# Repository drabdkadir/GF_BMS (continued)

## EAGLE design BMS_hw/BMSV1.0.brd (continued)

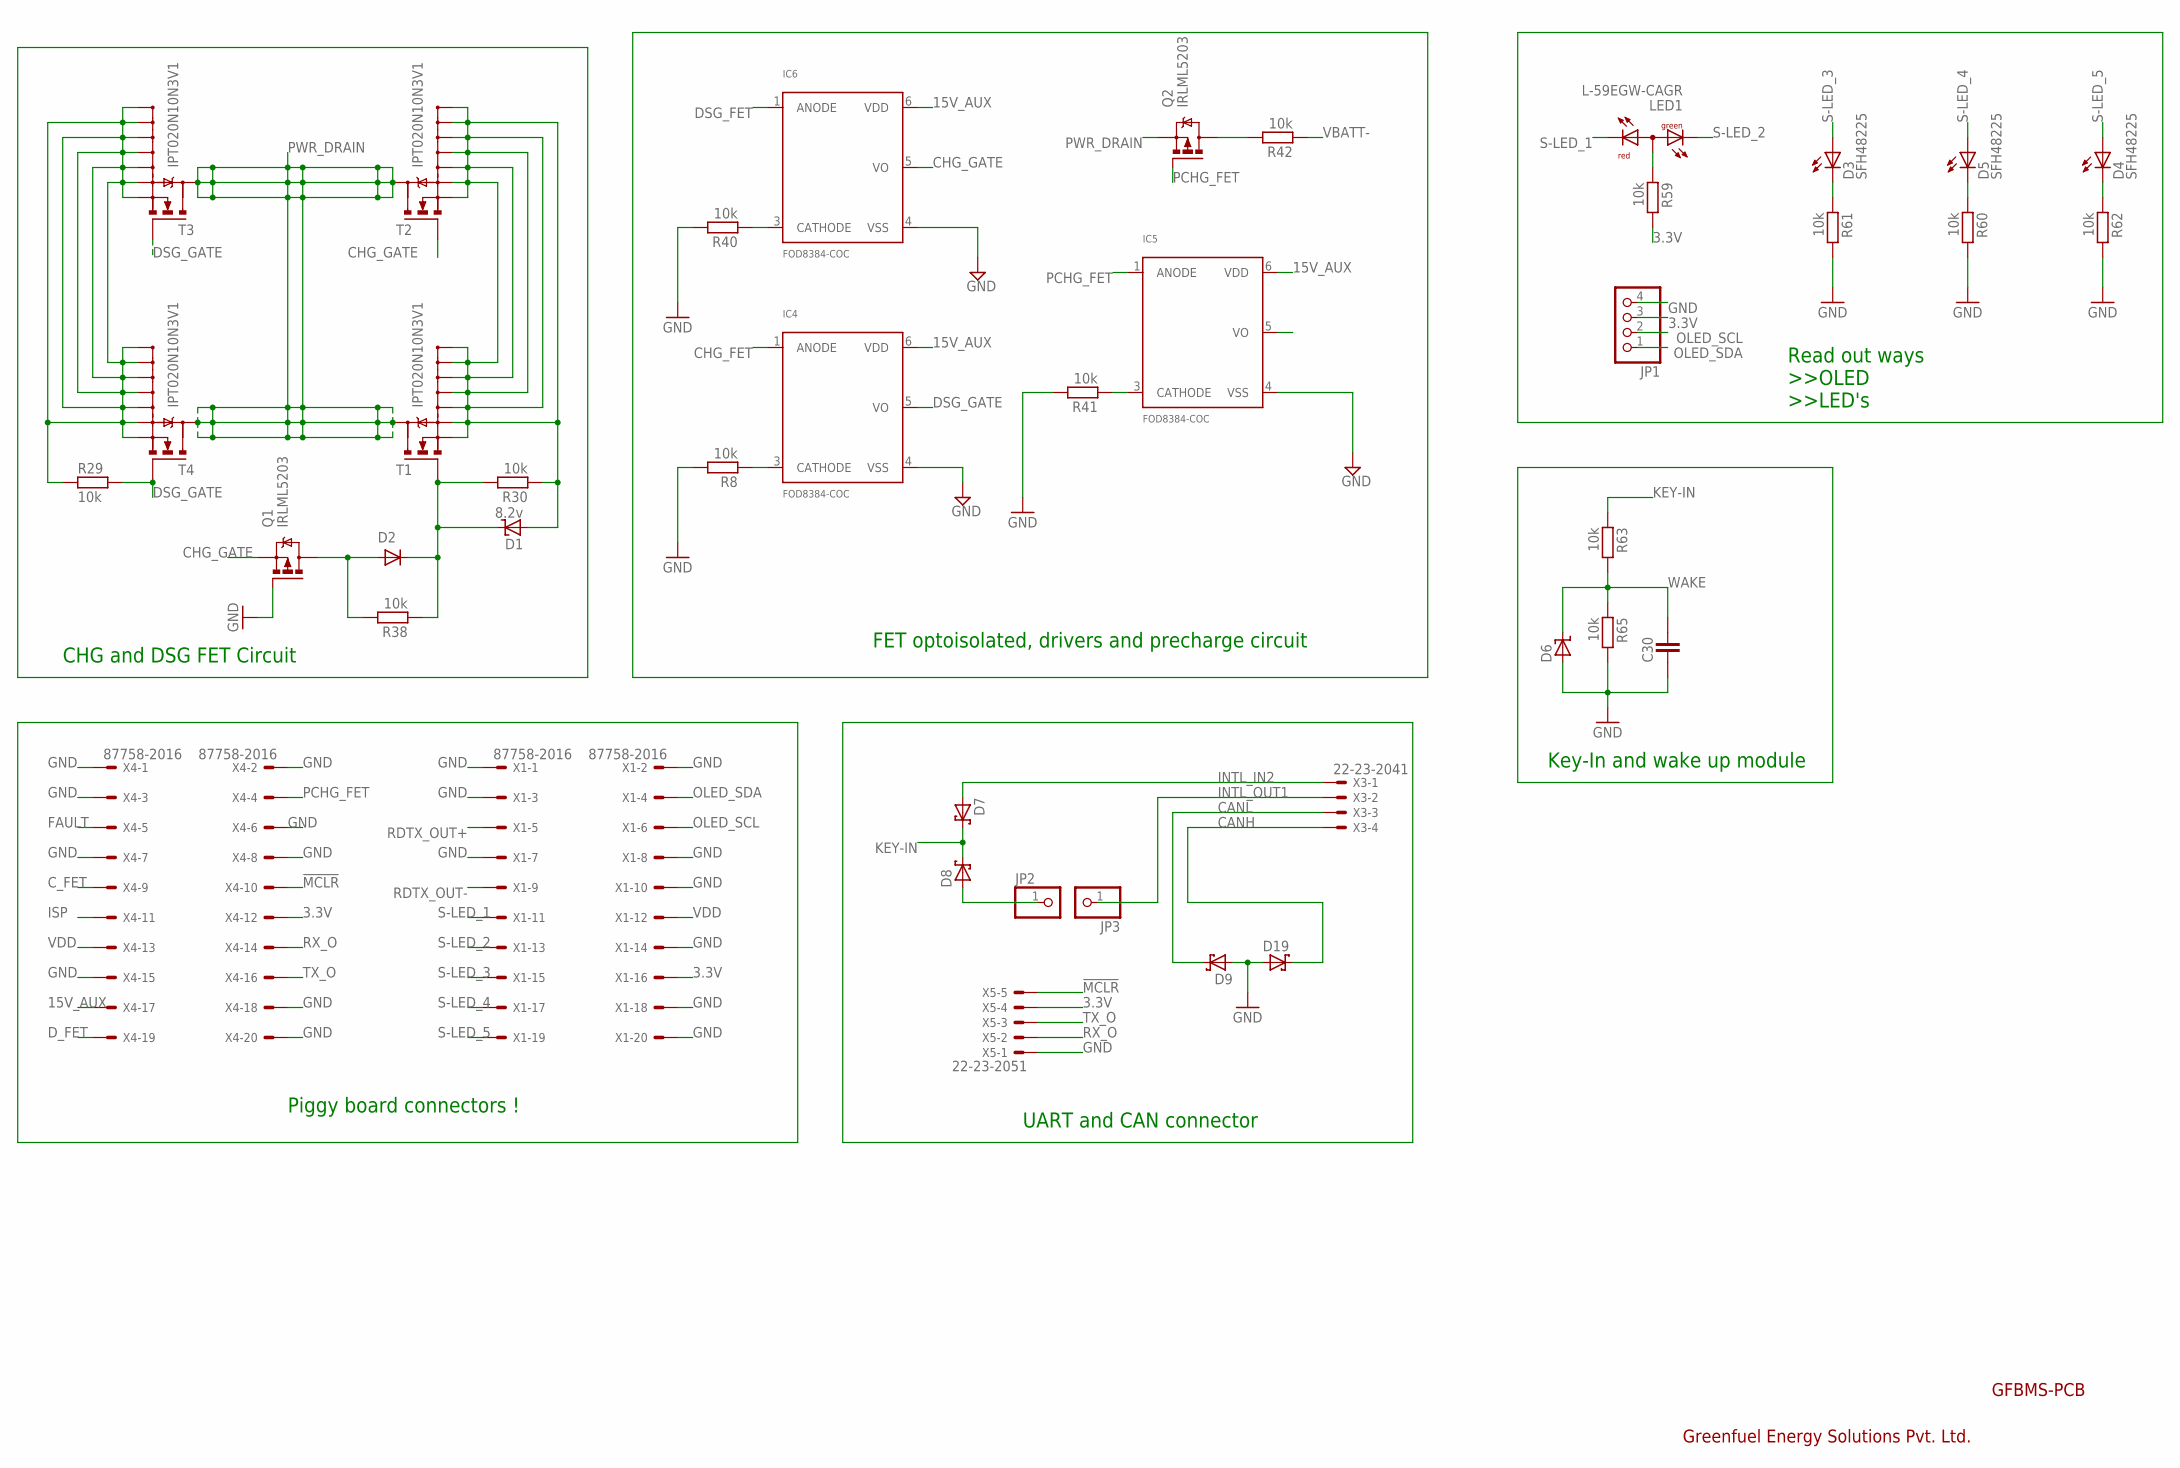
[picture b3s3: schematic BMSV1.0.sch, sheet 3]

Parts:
C30: CAPACITOR_0402; CAPC1005X60N
D1: 8.2v; SOD3718X135N
D2: DIODE_SOD-123; SOD3718X135N
D3, D4, D5: SFH48225; SFH482
D6: ZENER_SOD-123; SOD3718X135N
D7, D8, D9, D19: SCHOTTKY_SOD-123; SOD3718X135N
IC4, IC5, IC6: FOD8384-COC; SOP5
JP1: PINOLED-4; OLED-CON
JP2, JP3: PINHD-1X1CB; 1X01-CLEANBIG
LED1: L-59EGW-CAGR; L-59EGW-CA
Q1, Q2: IRLML5203; MICRO3
R8, R29, R30, R38, R40, R41, R42, R59, R60, R61, R62, R63, R65: 10k; RESC1005X40AN
T1, T2, T3, T4: IPT020N10N3V1; PG-HSOF-9
X1, X4: 87758-2016
X3: 22-23-2041
X5: 22-23-2051

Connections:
3.3V: JP1.3, R59.2, X1.16, X4.12, X5.4
15V_AUX: IC4.6 (VDD), IC5.6 (VDD), IC6.6 (VDD), X4.17
!MCLR: X4.10, X5.5
CANH: D19.K, X3.4
CANL: D9.K, X3.3
CHG_FET: IC4.1 (ANODE)
CHG_GATE: IC6.5 (VO), Q1.2 (S), T2.1 (G)
C_FET: X4.9
DSG_FET: IC6.1 (ANODE)
DSG_GATE: IC4.5 (VO), R29.2, T3.1 (G), T4.1 (G)
D_FET: X4.19
FAULT: X4.5
GND: C30.1, D6.A, D9.A, D19.A, IC4.4 (VSS), IC5.4 (VSS), IC6.4 (VSS), JP1.4, Q1.1 (G), R8.2, R40.2, R41.2, R60.2, R61.2, R62.2, R65.2, X1.1, X1.2, X1.3, X1.7, X1.8, X1.10, X1.14, X1.18, X1.20, X4.1, X4.2, X4.3, X4.6, X4.7, X4.8, X4.15, X4.18, X4.20, X5.1; also elsewhere on the board
INTL_IN2: D7.A, X3.1
INTL_OUT1: JP3.1, X3.2
ISP: X4.11
KEY-IN: D7.K, D8.K, R63.1
unnamed: D2.A, Q1.3 (D), R38.2
unnamed: IC4.3 (CATHODE), R8.1
unnamed: D1.K, D2.K, R30.2, R38.1, T1.1 (G)
unnamed: IC6.3 (CATHODE), R40.1
unnamed: IC5.3 (CATHODE), R41.1
unnamed: Q2.3 (D), R42.2
unnamed: R29.1, T3.2 (S), T3.3 (S1), T3.4 (S2), T3.5 (S3), T3.6 (S4), T3.7 (S5), T3.8 (S6), T4.2 (S), T4.3 (S1), T4.4 (S2), T4.5 (S3), T4.6 (S4), T4.7 (S5), T4.8 (S6)
unnamed: D1.A, R30.1, T1.2 (S), T1.3 (S1), T1.4 (S2), T1.5 (S3), T1.6 (S4), T1.7 (S5), T1.8 (S6), T2.2 (S), T2.3 (S1), T2.4 (S2), T2.5 (S3), T2.6 (S4), T2.7 (S5), T2.8 (S6)
unnamed: LED1.1 (A), R59.1
unnamed: D4.K (C), R62.1
unnamed: D5.K (C), R60.1
unnamed: D3.K (C), R61.1
unnamed: D8.A, JP2.1
OLED_SCL: JP1.2, X1.6
OLED_SDA: JP1.1, X1.4
PCHG_FET: IC5.1 (ANODE), Q2.1 (G), X4.4
PWR_DRAIN: Q2.2 (S), T1.9 (D), T2.9 (D), T3.9 (D), T4.9 (D)
RDTX_OUT+: X1.5; also elsewhere on the board
RDTX_OUT-: X1.9; also elsewhere on the board
RX_O: X4.14, X5.2
S-LED_1: LED1.3 (CR), X1.11
S-LED_2: LED1.2 (CG), X1.13
S-LED_3: D3.A, X1.15
S-LED_4: D5.A, X1.17
S-LED_5: D4.A, X1.19
TX_O: X4.16, X5.3
VBATT-: R42.1
VDD: X1.12, X4.13; also elsewhere on the board
WAKE: C30.2, D6.K, R63.2, R65.1

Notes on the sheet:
CHG and DSG FET Circuit
Read out ways >>OLED >>LED's
FET optoisolated, drivers and precharge circuit
Piggy board connectors !
GFBMS-PCB
Greenfuel Energy Solutions Pvt. Ltd.
Key-In and wake up module
UART and CAN connector

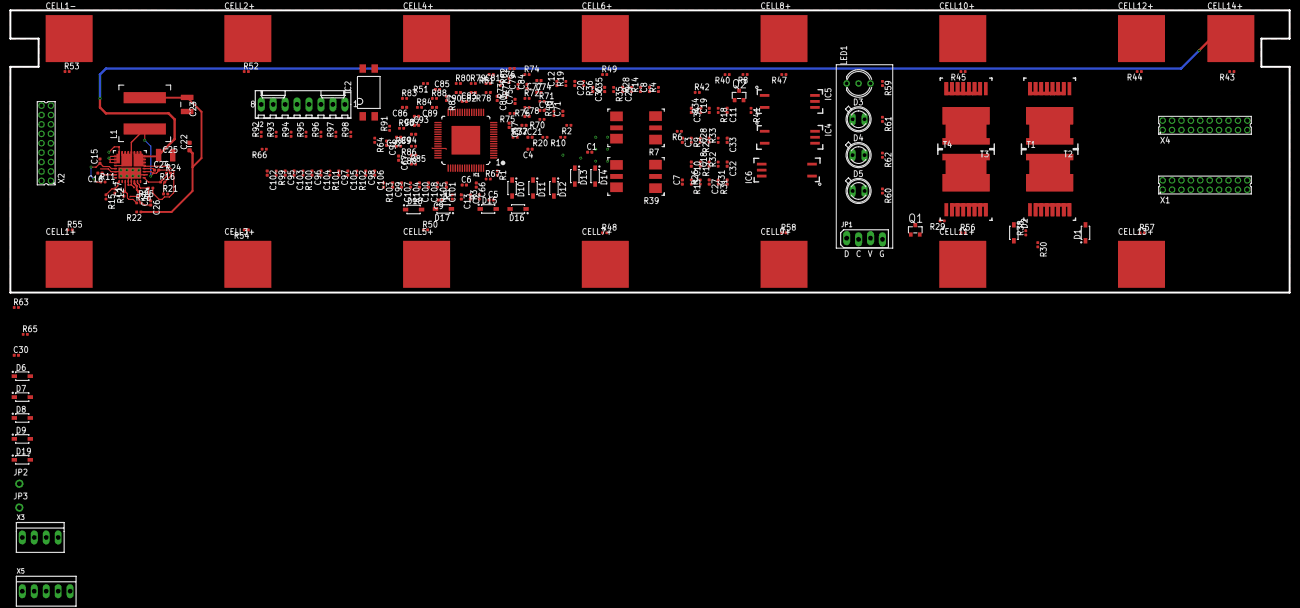
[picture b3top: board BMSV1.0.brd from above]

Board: 4 copper layers, 272.0 x 60.0 mm, 237 parts (0 on the bottom side), 151 nets.

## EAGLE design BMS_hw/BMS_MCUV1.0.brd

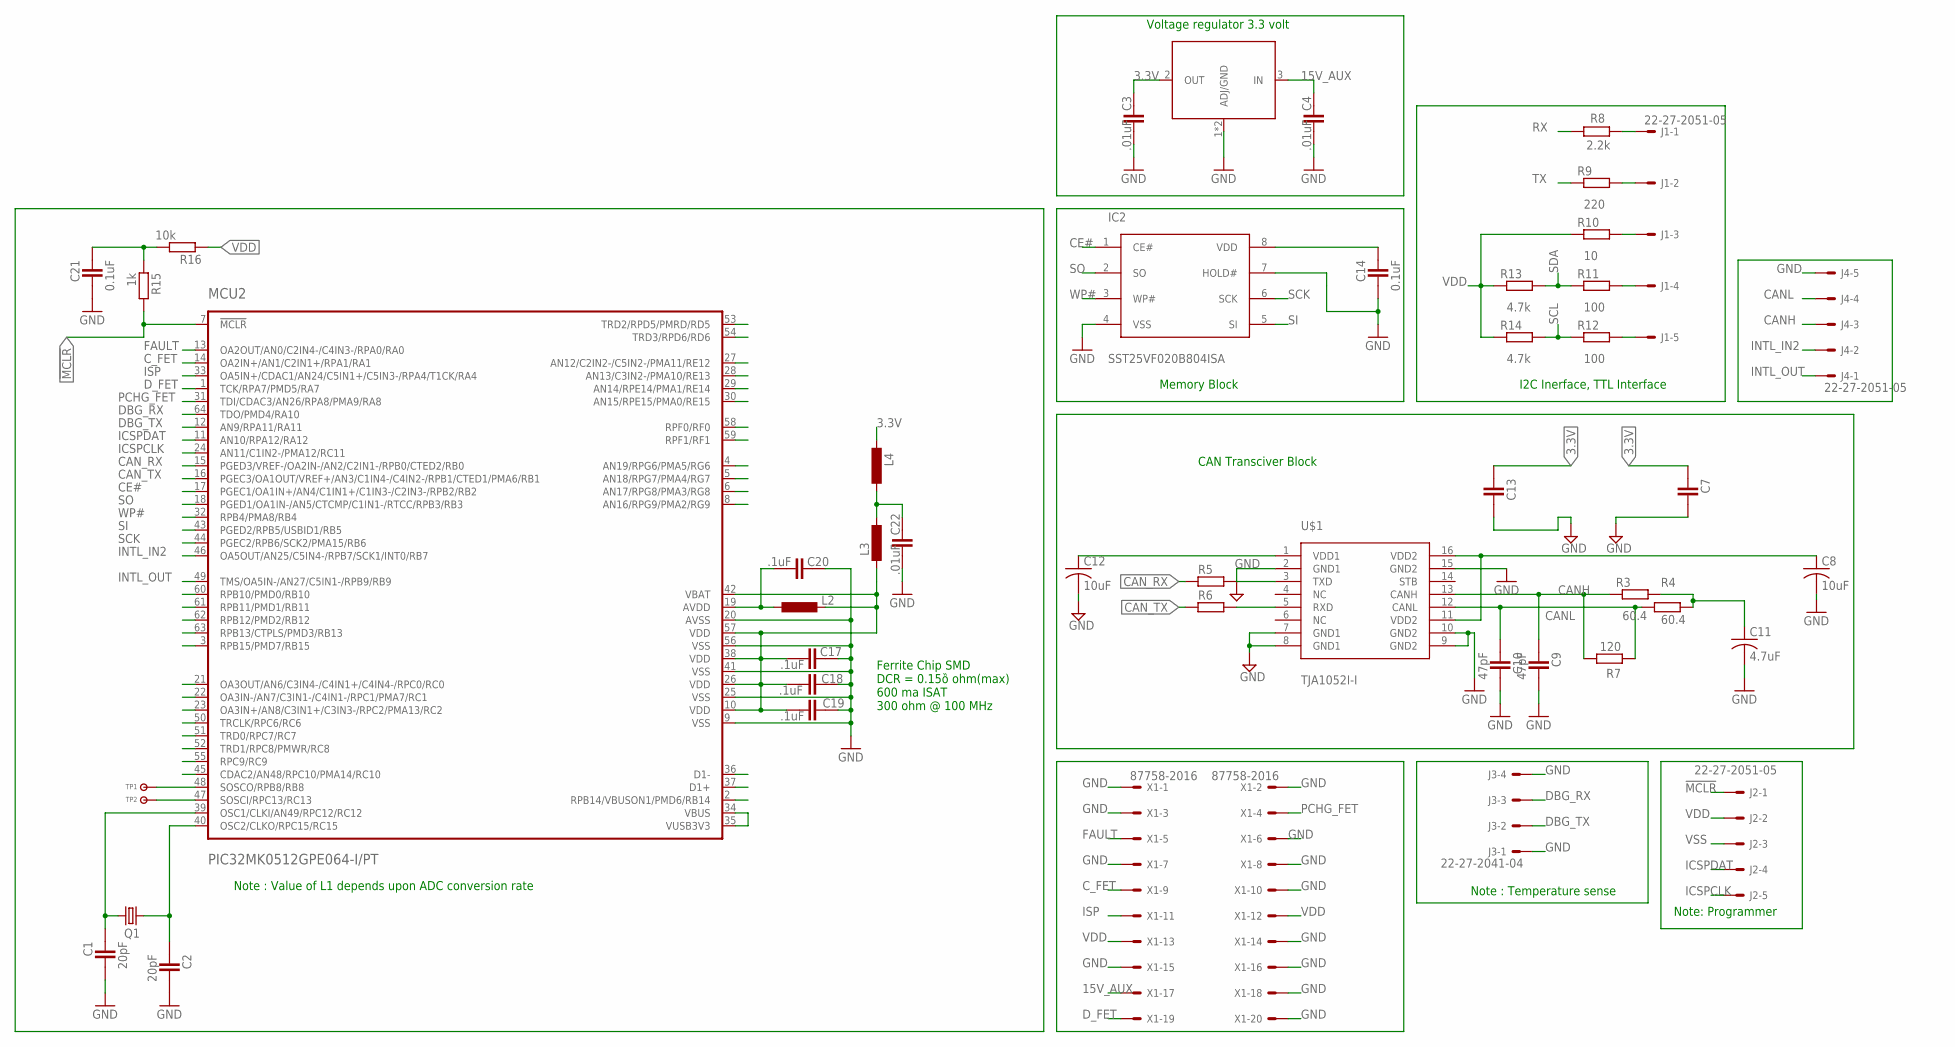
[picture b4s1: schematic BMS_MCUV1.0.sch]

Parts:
C1, C2: 20pF; CAPC1608X92N
C3, C4, C22: .01uF; CAPC1608X92N
C7, C13: CAPACITOR_0805; CAPC2012X145AN
C8, C12: 10uF; C0805
C9, C10: 47pF; CAPC2012X145AN
C11: 4.7uF; C0805
C14, C21: 0.1uF; CAPC1608X92N
C17, C18, C19, C20: .1uF; CAPC1608X92N
IC2: SST25VF020B804ISA; SOIC127P600X175-8N
J1, J2, J4: 22-27-2051-05; 6410-05
J3: 22-27-2041-04; 6410-04
L2, L3, L4: INDUCTOR_0603; INDC1608X95N
MCU2: PIC32MK0512GPE064-I/PT; TQFP-64-I/PT
Q1: CRYSTALCTS406; CTS406
R3, R4: 60.4; RESC2012X70N
R5, R6: RESISTOR_0805; RESC2012X70N
R7: 120; RESC2012X70N
R8: 2.2k; RESC2012X70N
R9: 220; RESC2012X70N
R10: 10; RESC2012X70N
R11, R12: 100; RESC2012X70N
R13, R14: 4.7k; RESC2012X70N
R15: 1k; RESC1608X55N
R16: 10k; RESC1608X55N
TP1, TP2: TP-SMD60
U1: NCP1117LP-PG; SOT-223
U$1: TJA1052I-I; SOT162-1
X1: 87758-2016

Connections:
3.3V: C3.2, C7.1, C13.1, L4.1, U1.2 (OUT)
15V_AUX: C4.2, U1.3 (IN), X1.17
!MCLR: J2.1, MCU2.7 (!MCLR), R15.2
CANH: C9.1, J4.3, R3.1, R7.2, U$1.13 (CANH)
CANL: C10.1, J4.4, R4.1, R7.1, U$1.12 (CANL)
CAN_RX: MCU2.15 (PGED3/VREF-/OA2IN-/AN2/C2IN1-/RPB0/CTED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), R5.1
CAN_TX: MCU2.16 (PGEC3/OA1OUT/VREF+/AN3/C1IN4-/C4IN2-/RP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), R6.1
CE#: IC2.1 (CE#), MCU2.17 (PGEC1/OA1IN+/AN4/C1IN1+/C1IN3-/C2IN3-/R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)
C_FET: MCU2.14 (OA2IN+/AN1/C2IN1+/RPA1/RA1), X1.9
DBG_RX: J3.3, MCU2.64 (TDO/PMD4/RA10)
DBG_TX: J3.2, MCU2.12 (AN9/RPA11/RA11)
D_FET: MCU2.1 (TCK/RPA7/PMD5/RA7), X1.19
FAULT: MCU2.13 (OA2OUT/AN0/C2IN4-/C4IN3-/RPA0/RA0), X1.5
GND: C1.2, C2.2, C3.1, C4.1, C7.2, C8.2, C9.2, C10.2, C11.2, C12.2, C13.2, C14.2, C17.2, C18.2, C19.2, C20.2, C21.2, C22.1, IC2.4 (VSS), IC2.7 (HOLD#), J3.1, J3.4, J4.5, MCU2.9 (VSS), MCU2.20 (AVSS), MCU2.25 (VSS), MCU2.41 (VSS), MCU2.56 (VSS), U1.1 (ADJ/GND), U1.4 (ADJ/GND), U$1.2 (GND1), U$1.7 (GND1), U$1.8 (GND1), U$1.9 (GND2), U$1.10 (GND2), U$1.15 (GND2), X1.1, X1.2, X1.3, X1.6, X1.7, X1.8, X1.10, X1.14, X1.15, X1.16, X1.18, X1.20
ICSPCLK: J2.5, MCU2.24 (AN11/C1IN2-/PMA12/RC11)
ICSPDAT: J2.4, MCU2.11 (AN10/RPA12/RA12)
INTL_IN2: J4.2, MCU2.46 (OA5OUT/AN25/C5IN4-/RPB7/SCK1/INT0/RB7)
INTL_OUT: J4.1, MCU2.49 (TMS/OA5IN-/AN27/C5IN1-/RPB9/RB9)
ISP: MCU2.33 (OA5IN+/CDAC1/AN24/C5IN1+/C5IN3-/RPA4/T1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), X1.11
unnamed: C1.1, MCU2.39 (OSC1/CLKI/AN49/RPC12/RC12), Q1.3 (2)
unnamed: C2.1, MCU2.40 (OSC2/CLKO/RPC15/RC15), Q1.1
unnamed: MCU2.48 (SOSCO/RPB8/RB8), TP1.P$1
unnamed: R6.2, U$1.5 (RXD)
unnamed: R5.2, U$1.3 (TXD)
unnamed: C12.1, U$1.1 (VDD1)
unnamed: C11.1, R3.2, R4.2
unnamed: C8.1, U$1.11 (VDD2), U$1.16 (VDD2)
unnamed: C14.1, IC2.8 (VDD)
unnamed: MCU2.47 (SOSCI/RPC13/RC13), TP2.P$1
unnamed: J1.1, R8.2
unnamed: J1.2, R9.2
unnamed: J1.3, R10.2
unnamed: J1.4, R11.2
unnamed: J1.5, R12.2
unnamed: C20.1, L2.1, MCU2.19 (AVDD)
unnamed: C22.2, L3.2, L4.2
unnamed: C21.1, R15.1, R16.2
unnamed: MCU2.34 (VBUS), MCU2.35 (VUSB3V3)
PCHG_FET: MCU2.31 (TDI/CDAC3/AN26/RPA8/PMA9/RA8), X1.4
RX: R8.1
SCK: IC2.6 (SCK), MCU2.44 (PGEC2/RPB6/SCK2/PMA15/RB6)
SCL: R12.1, R14.2
SDA: R11.1, R13.2
SI: IC2.5 (SI), MCU2.43 (PGED2/RPB5/USBID1/RB5)
SO: IC2.2 (SO), MCU2.18 (PGED1/OA1IN-/AN5/CTCMP/C1IN1-/RTCC/RPB3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)
TX: R9.1
VDD: C17.1, C18.1, C19.1, J2.2, L2.2, L3.1, MCU2.10 (VDD), MCU2.26 (VDD), MCU2.38 (VDD), MCU2.42 (VBAT), MCU2.57 (VDD), R10.1, R13.1, R14.1, R16.1, X1.12, X1.13
VSS: J2.3
WP#: IC2.3 (WP#), MCU2.32 (RPB4/PMA8/RB4)

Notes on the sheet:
Note : Value of L1 depends upon ADC conversion rate
CAN Transciver Block
Memory Block
Note: Programmer
I2C Inerface, TTL Interface
Note : Temperature sense
Ferrite Chip SMD DCR = 0.15ȍ ohm(max) 600 ma ISAT 300 ohm @ 100 MHz
Voltage regulator 3.3 volt

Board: 4 copper layers, 49 parts (0 on the bottom side), 46 nets, no tracks yet.

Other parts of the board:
X2, X3: KK-156-10

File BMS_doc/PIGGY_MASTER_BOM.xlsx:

GF_AFE board Revised: Sunday, OCT 14, 2018
SCH-XXXXX PDF: SPF-XXXXX Revision: 01
Item | Quantity | ASSY_OPT | Reference | Value | Description | ASSY_NOTE | Mfg Name | Mfg Part Number | PCB Footprint
 | 1 |  | LED1
 | 1 |  | Q8
 | 1 |  | JP2
 | 2 |  | JP1, JP5
 | 1 |  | C22 | .01uF
 | 4 |  | C17, C18, C19, C20 | .1uF
 | 2 |  | C14, C21 | 0.1uF
 | 2 |  | R5, R6 | 0E
 | 2 |  | R11, R12 | 100R
 | 1 |  | R16 | 10k
 | 3 |  | C8, C12, C13 | 10uF
 | 1 |  | R7 | 120
 | 1 |  | R15 | 1k
 | 2 |  | C1, C2 | 20pF
 | 2 |  | R1, R115 | 330E
 | 2 |  | R13, R14 | 4.7k
 | 1 |  | C11 | 4.7uF
 | 2 |  | C9, C10 | 47pF
 | 2 |  | R3, R4 | 60.4
 | 1 |  | Q1 | CRYSTALS-GND-LID-IQXC-42
 | 3 |  | L2, L3, L4 | MMZ2012R301ATD25
 | 1 |  | MCU2 | PIC32MK0512GPE064-I/PT
 | 1 |  | IC2 | SST25VF020B804ISA
 | 1 |  | U$1 | TJA1052I-I
 | 5 |  | TP1, TP2, TP3, TP4, TP5 | TP-SMD60

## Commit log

2018-09-18 ADDED NEW DOC FOR TEST
2018-09-18 PIC32MK0512GPE064 part footprint created!
2018-09-18 connected SPI enable to VCOM
2018-09-18 added git ignore added
2018-09-18 VQFN-32 package footprint created!
2018-09-18 VQFN-32 footprint
    Pads nroundness and dimensioins changed.
2018-09-18 updated after NXP review
2018-09-18 added .s ignor files
2018-09-18 ignore .b files
2018-09-18 ignore
2018-09-18 on track value and name mark on the package TQFP64
2018-09-18 MCU Microchip schematic started
2018-09-18 MCU device prefix updated
2018-09-18 VQFN-32 foot-print
    VQFN-32 pads rearranged, all exposed thermal pads made, review required!
2018-09-18 update library ignore mcu
2018-09-18 sch saved
2018-09-18 Revert "update"
    This reverts commit aa4049f778983259dc345aca45d1d23f36a1eae3, reversing
    changes made to 483740ef09295ff9bd4c0bb0f0003845ed3d2f73.
2018-09-18 Revert "sch saved"
    This reverts commit 483740ef09295ff9bd4c0bb0f0003845ed3d2f73.
2018-09-18 Revert "Merge branch 'hw' of https://github.com/kunal-GF/GF_BMS into hw"
    This reverts commit cb819c5a256ea6b478828d222d8978a164d41654, reversing
    changes made to 1a0582993ac0a8851db6f9d974378484a723c9b0.
2018-09-18 Libray reinstalled
2018-09-18 Prefix of MCU PIC changed
2018-09-18 tocu layer deleted
2018-09-18 PIC MCU PIN PADS RESIZED
2018-09-18 Upper row of PIC MCU pads rellocated
2018-09-18 Silkscreen and other 3 sides are reallocated
2018-09-18 tdocu and silk reallocated in PIC MCU
2018-09-18 pic mcu silkscreen width changed
2018-09-18 PIC MCU tdocu completed
2018-09-18 VQFN-32 footprint created
2018-09-18 VQFN-32 pads created
2018-09-18 VQFN_32 pads renumbered
2018-09-18 pads of VQFN-32 are reallocated
    diverted to reallocated off track MCU PIC NAME and VALUE
2018-09-18 PIC MCU name and value repostioned
2018-09-18 MCU placed sch
2018-09-18 VQFN-32 side pads re-allocated
2018-09-18 VQFN-32 all pads reallocated correctly
2018-09-18 VQFN-32 , 33 SOLDER PAD ADDED
2018-09-18 PIC32MK symbol in naming changed
2018-09-18 33 pad of VQFN-32 placed
2018-09-18 VQFN-32 , 33 pin pad removed
2018-09-18 vss and vdd pin rearranged in PIC mCU
2018-09-18 VQFN-32, full footprint or land pattern updated
2018-09-18 MIC28515 symbol created
2018-09-19 MIC28515 pins renamed
2018-09-19 MIC28515 name and values added
2018-09-19 VQFN-32 name and value layer changed
2018-09-19 MIC28515, PIN directions changed
2018-09-19 PIC MCU MK pins rearranged
2018-09-19 MIC28515 DEVICE CREATED
2018-09-19 PG-HSOF
2018-09-19 GF_BMS_PAD created
2018-09-19 GF_BMS_pad footprint created
2018-09-19 GF_BMS_pad symbol created
2018-09-19 GF_BMS pad device created
2018-09-19 PG-HSOF pads renumbered
2018-09-19 PG-HSOF pads x axis rallocated
2018-09-19 PG-HSOF package y axis reaaranged
2018-09-19 PG-HSOF footprint reallocated and redefined
2018-09-19 Cell terminal pad replaced with specified size
2018-09-19 cell terminal pads are placed according to design
2018-09-19 PG-HSOF TODCU layer added
2018-09-19 PG-HSOF solder mask added
2018-09-19 PG-HSOF changes rearranged
2018-09-19 pads sizes of infeonon mosfet n channel changed
2018-09-19 final release of PG-HSOF footprint
2018-09-19 IPT020N10N3 symbol created and pin nomencleature done !
2018-09-19 direction of IPT020N10N3 part done
2018-09-19 IPT020N10N3 device created
2018-09-19 ignored pro files
2018-09-19 board updated cell name and value
2018-09-19 board schematic names and values changed
2018-09-19 library name and values of GF_BMS_PAD updated
2018-09-19 GF_BMS_CELL PAD CHANGED TO CELL PAD
2018-09-19 coordinates of PIC MCU changed
2018-09-19 updated MCU schematic
2018-09-19 library description updated
2018-09-19 git ignore epf file
2018-09-19 gf_bms_ hw v1.0 board layout names and values changed
2018-09-19 Schematic componenet out of track are being retracked
2018-09-19 hot plug protection and other protection schematic offgrid corrected
2018-09-19 hot plug protection and filters board regrid done !
2018-09-20 Buck convertor schematic added on page 2
2018-09-20 buck convertor is added to board layout
2018-09-20 Buck convertor schematic complete calaculation required!
2018-09-20 Buck convertor board layout complete routing required!
2018-09-21 consistancy recovere and new sheet added for power sch
2018-09-21 added frame
2018-09-21 mosfet off grid rearranged
2018-09-21 push_11_22_21_09_2018
2018-09-22 push_2
2018-09-22 push_3
2018-09-22 eagl eproject file updated
2018-09-23 gate pull up diode added in schematic and board
2018-09-23 chg and dsg mosfet circuit final submission
2018-09-23 mosfet drawing updated with candy
2018-09-23 push @@@21
2018-09-23 brd,sch,lbr
2018-09-23 mosfet final me se final
2018-09-24 dc-dc convertor library schematic and board layout completed final submitt!
2018-09-24 commit changes
2018-09-25 LRMAP3920 smd fuse library created! AR
2018-09-25 dcdcdcdc
2018-09-25 ldo library created
2018-09-25 mcu ldo circuit build ok
2018-09-25 board mcu itt 1
2018-09-25 board placment complete rough! mcu board
2018-09-25 ATR1
2018-09-26 erroe removed
2018-09-26 2 error removed in mcu board
2018-09-26 DRC setup
2018-09-26 change package to 0603
2018-09-26 package udated
2018-09-26 baord sdsahdj
2018-09-26 no drc on mcu board
2018-09-26 defsdf
2018-09-26 optocoupler foot-print craeted!
2018-09-27 Invalid polygon in gf board
2018-09-27 secondary osc removed
2018-09-27 board finnnnalo
2018-09-27 layout airwire reduced
2018-09-27 via added
2018-09-27 all clearnance done !
2018-09-28 brd sch and lbr of vqfn-32 updated, error resolved !
2018-09-28 sch brd lib placment comptd!
2018-09-29 brd lbr sch updated to new version
2018-09-29 added gate calculator, AFE datasheet, ref schematic AFE
2018-09-30 placment 80% done
2018-09-30 CAN communication protocol DOC swapping battery architecture
2018-09-30 jesper's BMS board schematic
2018-10-01 buck routing complete !
2018-10-01 afe block placement completed , buck convertor routing 90% done !
2018-10-01 added diffrent project filr for MCU and AFE pcb
2018-10-01 Testing git bash trial !
2018-10-01 design rule file for 2 layer board
2018-10-01 boar updated !
2018-10-01 DRU files added to DOC folder
2018-10-01 added afe datasheet
2018-10-02 power planes created !
2018-10-02 added BOM and DCDC datasheet updated dcdc shematic
2018-10-02 BOM and ferrite datasheet added
2018-10-02 @1 updtae !
2018-10-02 updated dcdc sch
2018-10-02 updated sch
2018-10-03 board layout itt@1
2018-10-03 updated schematic inductor part no 3.3 5v ldo net naaming
2018-10-03 afe board and schematic files are updatd !
2018-10-03 dcd eval board and AFE BOM updated
2018-10-03 brd, lyout changed
2018-10-04 @AFE board and layout afe itt@3
2018-10-04 brd : layout :sch update@4
2018-10-04 part no update
2018-10-04 itt@5
2018-10-04 itt@6 itt@6
2018-10-04 itt@7
2018-10-04 updated part no
2018-10-05 afe bom part added
2018-10-05 itt@8
2018-10-05 itt @ coil-craft MSS library created, @afe layout 90% complete ! @schhematic altr @3!
2018-10-06 board afe and layout
2018-10-06 aaaaaaaaaaaaaa
2018-10-06 added research paper on EV battery tech
2018-10-06 @ITT9
2018-10-06 @board layout schmeatic itt@10
2018-10-06 hjhk
2018-10-07 asdasd
2018-10-07 ITT@112
2018-10-07 brd layout and sch updated!
2018-10-08 board layout and schematic files updated@12
2018-10-08 brd layout and sch update @14
2018-10-08 @itt@17
2018-10-09 @dsdwsw
2018-10-09 bom afe part added
2018-10-09 afe mcu schematic updated
2018-10-10 dwdhshs
2018-10-10 afe board itt@18
2018-10-10 afe board itt@19
2018-10-10 afe ver 1.1 added@itt@20
2018-10-11 itt@21
2018-10-12 updated sch with diff AFE version1.1
2018-10-13 replace part with fod8384 with tlp152 added datasheet in doc folder
2018-10-14 TLP152 COUPLER library added
2018-10-14 pdf TLP152 name changed
2018-10-14 afe and piggy board bom layout and schematic all changed for final only dc-dc convertor replacement required !
2018-10-14 Afe board updated dc dc convertor
2018-10-14 AFE master bom itt, layout itt, sch itt
2018-10-14 afe board layout and schematic alt!
2018-10-14 afe master bom ediited
2018-10-14 afe and piggy sch layout itt!
2018-10-15 bom updated
2018-10-15 4.04mm space released from componrnrts for slidding!
2018-10-18 removed single page sch pdf
2018-10-18 last
2018-10-18 board schematic and part updated
2018-10-18 ZXMP10A17G part added to GreenFuel library !
2018-10-18 sch board updated
2018-10-20 mcu bom board and schematic updated !
2018-10-20 updated afe shmetatic rectification stage of MCU PCB
2018-10-20 pa channel mosfet 80v 2.2a
2018-10-20 AFE updated BOM
2018-10-20 xcel sheet
2018-10-21 pdf , brd and sch itt@26
2019-01-02 fdghfn
2019-01-02 piggy top layer routed 50%
2019-01-02 fhyffj
2019-01-02 fryfjhf
2019-01-02 gugjkvjkgj
